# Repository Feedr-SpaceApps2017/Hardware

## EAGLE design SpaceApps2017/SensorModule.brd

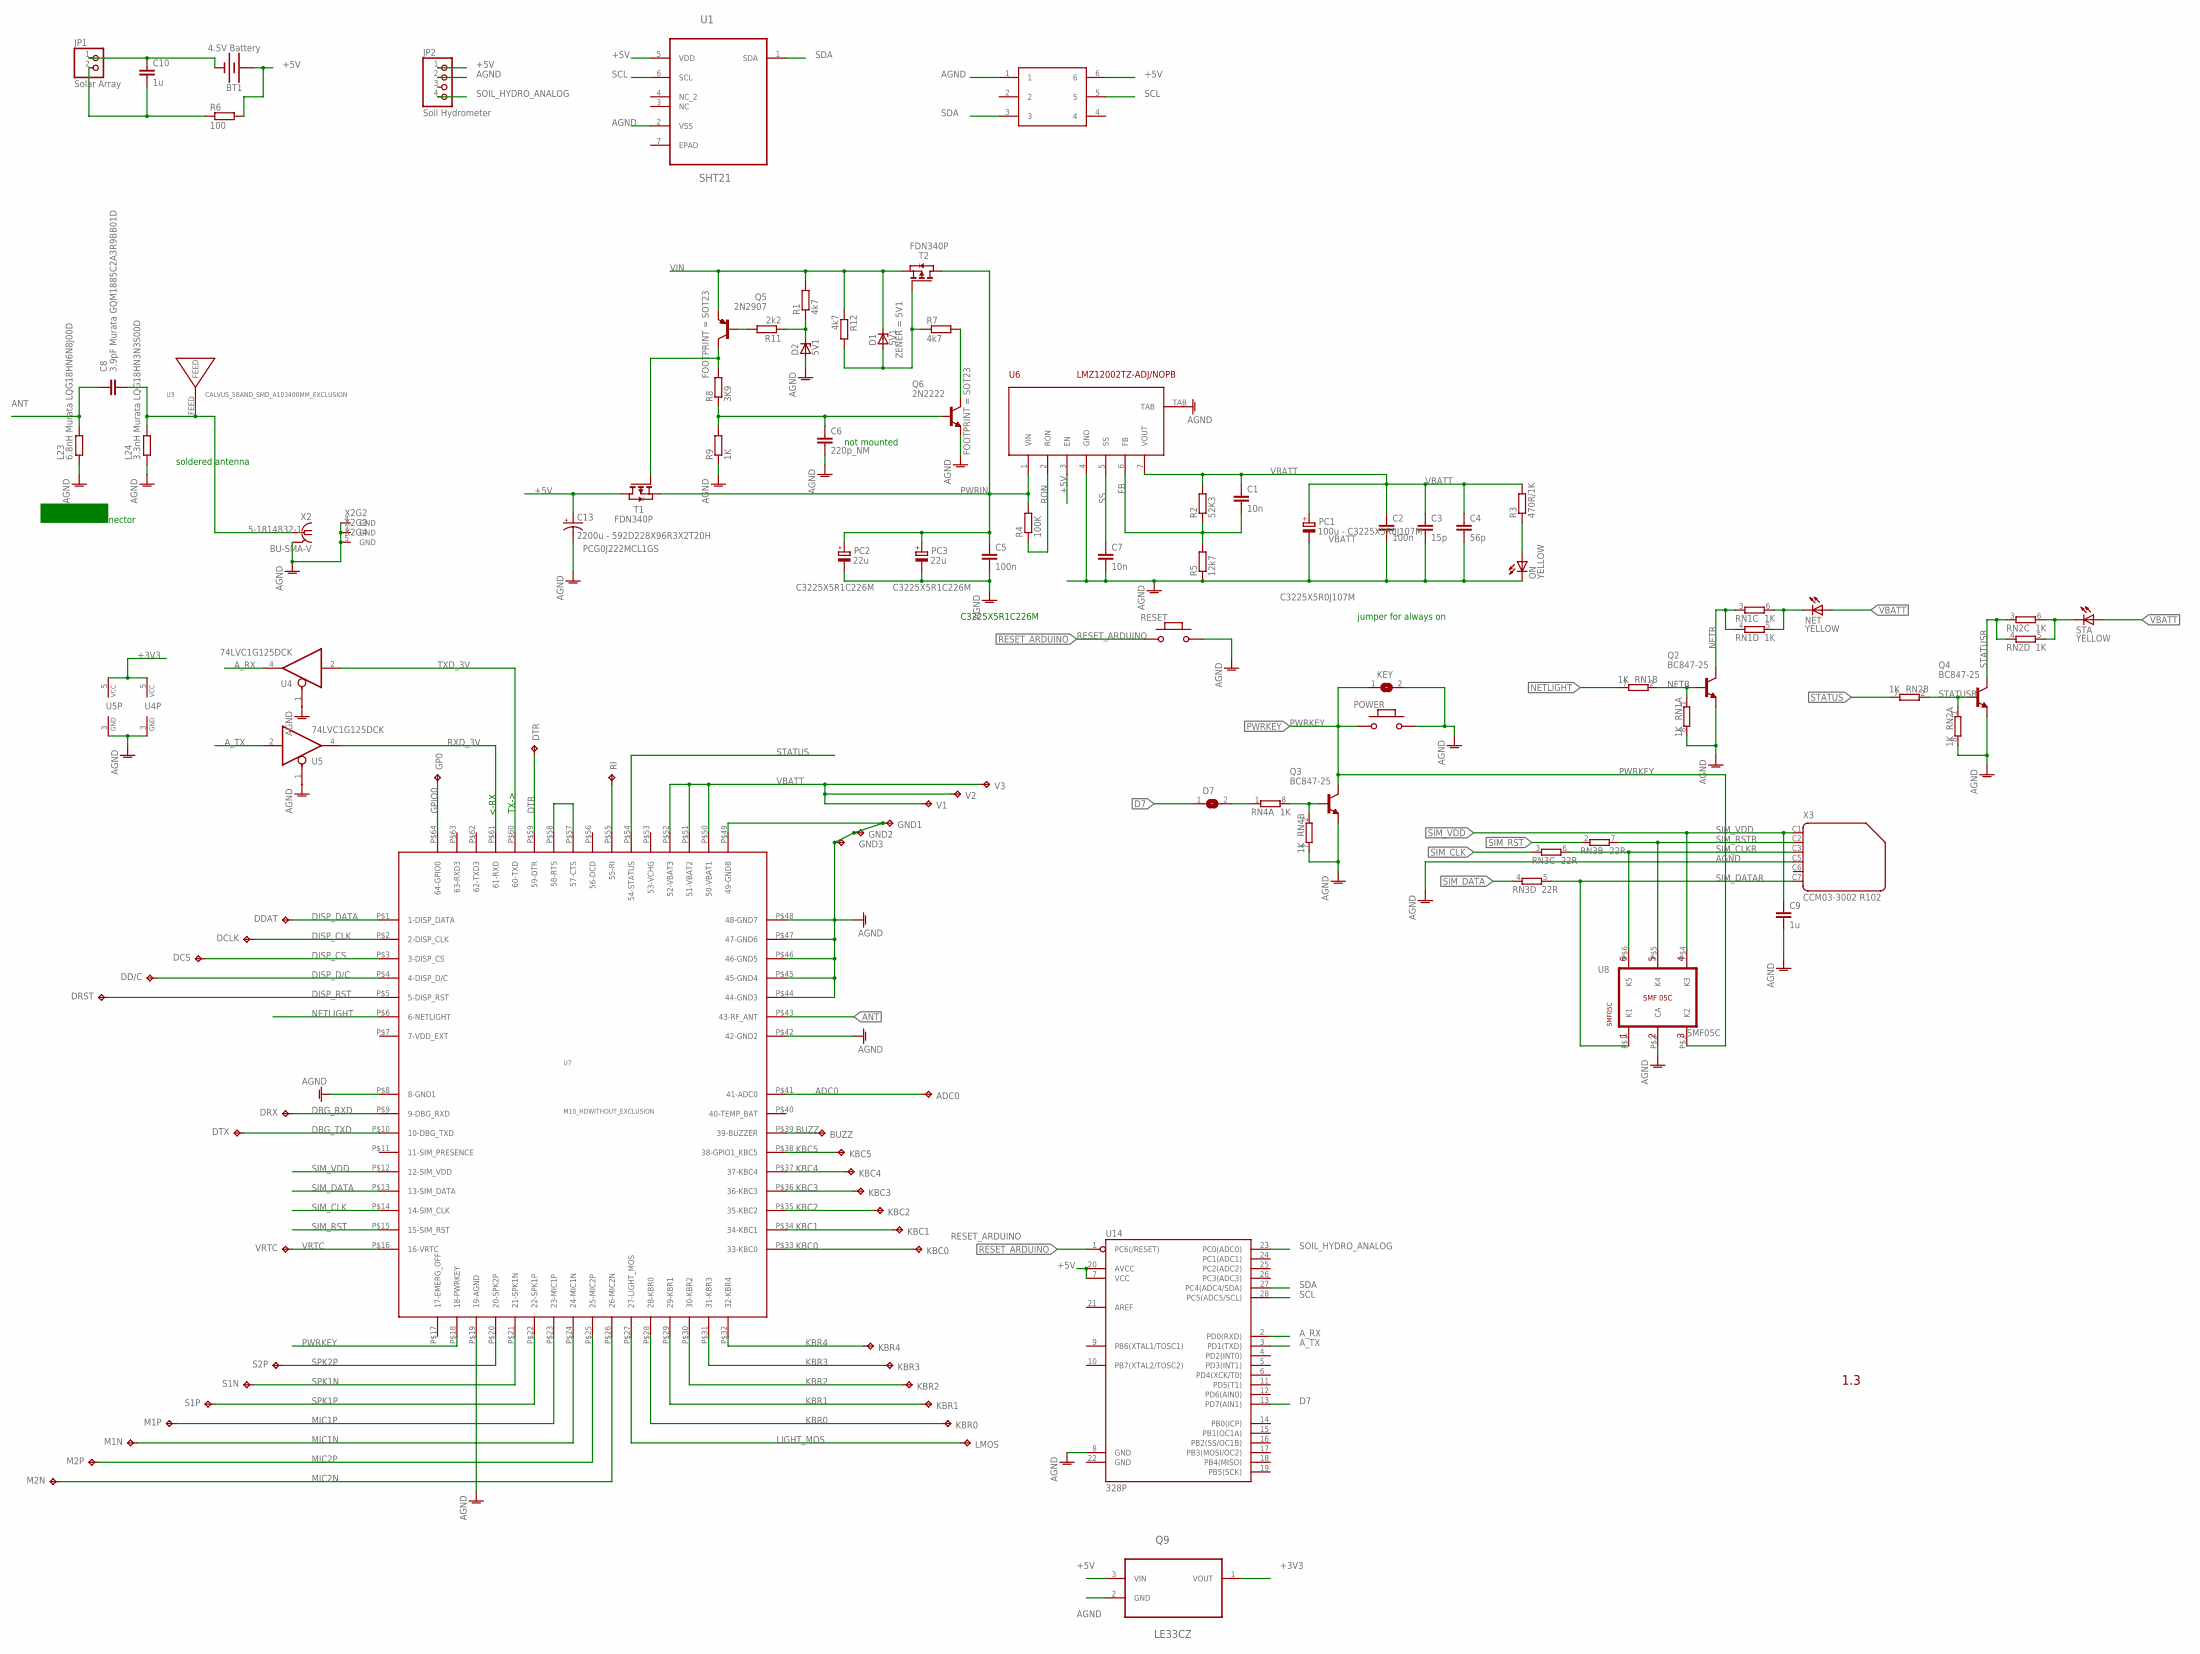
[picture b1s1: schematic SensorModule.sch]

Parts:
ADC0: TPPAD1-09; P1-09
BT1: 4.5V Battery; BATTERY-AA
BUZZ: TPPAD1-09; P1-09
C1, C7: 10n; C0603-ROUND
C2, C5: 100n; C0603-ROUND
C3: 15p; C0603-ROUND
C4: 56p; C0603-ROUND
C6: 220p_NM; C0603-ROUND
C8: 3.9pF Murata GQM1885C2A3R9BB01D; C0603-ROUND
C9: 1u; C0603-ROUND
C10: 1u; C0201
C13: 2200u - 592D228X96R3X2T20H; 085CS_1AW
D1, D2: 5V1; SMB
D7: SJ
DCLK: TPPAD1-09; P1-09
DCS: TPPAD1-09; P1-09
DD/C: TPPAD1-09; P1-09
DDAT: TPPAD1-09; P1-09
DRST: TPPAD1-09; P1-09
DRX: TPPAD1-09; P1-09
DTR: TPPAD1-09; P1-09
DTX: TPPAD1-09; P1-09
GND1, GND2, GND3: TPPAD1-09; P1-09
GP0: TPPAD1-09; P1-09
JP1: Solar Array; 1X02
JP2: Soil Hydrometer; 1X04
KBC0, KBC1, KBC2, KBC3, KBC4, KBC5: TPPAD1-09; P1-09
KBR0, KBR1, KBR2, KBR3, KBR4: TPPAD1-09; P1-09
KEY: SJ
L23: 6.8nH Murata LQG18HN6N8J00D; R0603-ROUND
L24: 3.3nH Murata LQG18HN3N3S00D; R0603-ROUND
LMOS: TPPAD1-09; P1-09
M1N, M1P, M2N, M2P: TPPAD1-09; P1-09
NET: YELLOW; CHIP-LED0805
ON: YELLOW; CHIP-LED0805
PC1: 100u - C3225X5R0J107M; SMC_B
PC2, PC3: 22u; SMC_B
POWER: MYSMD_PB157; SMD_157SW
Q2, Q3, Q4: BC847-25; SOT23-BEC
Q5: 2N2907; SOT23-BEC
Q6: 2N2222; SOT23-BEC
Q9: LE33CZ; TO127P254X749-3
R1, R7, R12: 4k7; R0603-ROUND
R2: 52K3; R0603-ROUND
R3: 470R/1K; R0603-ROUND
R4: 100K; R0603-ROUND
R5: 12k7; R0603-ROUND
R6: 100; R0201
R8: 3K9; R0603-ROUND
R9: 1K; R0603-ROUND
R11: 2k2; R0603-ROUND
RESET: MYSMD_PB157; SMD_157SW
RI: TPPAD1-09; P1-09
RN1, RN2, RN4: 1K; CAY16
RN3: 22R; CAY16
S1N, S1P, S2P: TPPAD1-09; P1-09
STA: YELLOW; CHIP-LED0805
T1, T2: FDN340P; SOT-23
U1: SHT21; DFN300X300X110-7N
U3: CALVUS_5BAND_SMD_A103400MM_EXCLUSION; CALVUS_5BAND_SMD_A10340_0MM_EXCLUSION
U4, U5: 74LVC1G125DCK; SC70-5
U6: LMZ12002TZ-ADJ/NOPB; TZA-7
U7: M10_HDWITHOUT_EXCLUSION; M10_HD_WITHOUT_EXCLUSION
U8: SMF05C; SC70_6L
U14: 328P; DIP28
U$1: VISHAY_VEML6070; SOT-23-6
V1, V2, V3: TPPAD1-09; P1-09
VRTC: TPPAD1-09; P1-09
X2: BU-SMA-V
X3: CCM03-3002 R102; CON-AMPHENOL_C707_10M006_512_2

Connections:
+3V3: Q9.1 (VOUT), U4.5 (VCC), U5.5 (VCC)
+5V: BT1.PWR@1 (+), C13.+, JP2.1, Q9.3 (VIN), R6.2, T1.1 (D), U1.5 (VDD), U6.3 (EN), U14.7 (VCC), U14.20 (AVCC), U$1.6
ADC0: ADC0.TP, U7.P$41 (41-ADC0)
AGND: BT1.GND@1 (-), C2.2, C3.2, C4.2, C5.2, C6.2, C7.2, C9.2, C10.1, C13.-, D2.A, GND1.TP, GND2.TP, GND3.TP, JP1.1, JP2.2, KEY.2, L23.1, L24.1, ON.C, PC1.-, PC2.-, PC3.-, POWER.2, Q2.E, Q3.E, Q4.E, Q6.E, Q9.2 (GND), R5.1, R9.1, RESET.2, RN1.8 (2), RN2.8 (2), RN4.7 (2), U1.2 (VSS), U4.1 (OE), U4.3 (GND), U5.1 (OE), U5.3 (GND), U6.4 (GND), U6.TAB, U7.P$8 (8-GND1), U7.P$19 (19-AGND), U7.P$42 (42-GND2), U7.P$44 (44-GND3), U7.P$45 (45-GND4), U7.P$46 (46-GND5), U7.P$47 (47-GND6), U7.P$48 (48-GND7), U7.P$49 (49-GND8), U8.P$2 (CA), U14.8 (GND), U$1.1, X2.2 (GND), X2.3 (GND), X2.4 (GND), X2.5 (GND), X3.C5 (4)
ANT: C8.1, L23.2, U7.P$43 (43-RF_ANT)
ANTENA: C8.2, L24.2, U3.FEED, X2.1
A_RX: U4.4 (O), U14.2 (PD0(RXD))
A_TX: U5.2 (I), U14.3 (PD1(TXD))
BUZZ: BUZZ.TP, U7.P$39 (39-BUZZER)
D7: D7.1, U14.13 (PD7(AIN1))
DBG_RXD: DRX.TP, U7.P$9 (9-DBG_RXD)
DBG_TXD: DTX.TP, U7.P$10 (10-DBG_TXD)
DISP_CLK: DCLK.TP, U7.P$2 (2-DISP_CLK)
DISP_CS: DCS.TP, U7.P$3 (3-DISP_CS)
DISP_D/C: DD/C.TP, U7.P$4 (4-DISP_D/C)
DISP_DATA: DDAT.TP, U7.P$1 (1-DISP_DATA)
DISP_RST: DRST.TP, U7.P$5 (5-DISP_RST)
DTR: DTR.TP, U7.P$59 (59-DTR)
FB: C1.2, R2.1, R5.2, U6.6 (FB)
GPIO0: GP0.TP, U7.P$64 (64-GPIO0)
KBC0: KBC0.TP, U7.P$33 (33-KBC0)
KBC1: KBC1.TP, U7.P$34 (34-KBC1)
KBC2: KBC2.TP, U7.P$35 (35-KBC2)
KBC3: KBC3.TP, U7.P$36 (36-KBC3)
KBC4: KBC4.TP, U7.P$37 (37-KBC4)
KBC5: KBC5.TP, U7.P$38 (38-GPIO1_KBC5)
KBR0: KBR0.TP, U7.P$28 (28-KBR0)
KBR1: KBR1.TP, U7.P$29 (29-KBR1)
KBR2: KBR2.TP, U7.P$30 (30-KBR2)
KBR3: KBR3.TP, U7.P$31 (31-KBR3)
KBR4: KBR4.TP, U7.P$32 (32-KBR4)
LIGHT_MOS: LMOS.TP, U7.P$27 (27-LIGHT_MOS)
MIC1N: M1N.TP, U7.P$24 (24-MIC1N)
MIC1P: M1P.TP, U7.P$23 (23-MIC1P)
MIC2N: M2N.TP, U7.P$26 (26-MIC2N)
MIC2P: M2P.TP, U7.P$25 (25-MIC2P)
unnamed: C10.2, JP1.2, R6.1
unnamed: ON.A, R3.1
unnamed: Q3.B, RN4.2 (1), RN4.8 (2)
unnamed: U7.P$57 (57-CTS), U7.P$58 (58-RTS)
unnamed: D7.2, RN4.1
unnamed: RI.TP, U7.P$55 (55-RI)
unnamed: Q5.C, R8.2, T1.3 (G)
unnamed: Q6.C, R7.2
unnamed: C6.1, Q6.B, R8.1, R9.2
unnamed: Q5.B, R11.2
unnamed: D1.A, R7.1, R12.2, T2.3 (G)
unnamed: D2.C, R1.1, R11.1
NETB: Q2.B, RN1.1, RN1.2 (1)
NETL: NET.C, RN1.5 (2), RN1.6 (2)
NETLIGHT: RN1.7 (2), U7.P$6 (6-NETLIGHT)
NETR: Q2.C, RN1.3 (1), RN1.4 (1)
PWRIN: C5.1, PC2.+, PC3.+, R4.2, T1.2 (S), T2.1 (D), U6.1 (VIN)
PWRKEY: KEY.1, POWER.1, Q3.C, U7.P$18 (18-PWRKEY), U8.P$3 (K2)
RESET_ARDUINO: RESET.1, U14.1 (PC6(/RESET))
RON: R4.1, U6.2 (RON)
RXD_3V: U5.4 (O), U7.P$61 (61-RXD)
SCL: U1.6 (SCL), U14.28 (PC5(ADC5/SCL)), U$1.5
SDA: U1.1 (SDA), U14.27 (PC4(ADC4/SDA)), U$1.3
SIM_CLK: RN3.3 (1), U7.P$14 (14-SIM_CLK)
SIM_CLKR: RN3.6 (2), U8.P$6 (K5), X3.C3 (3)
SIM_DATA: RN3.4 (1), U7.P$13 (13-SIM_DATA)
SIM_DATAR: RN3.5 (2), U8.P$1 (K1), X3.C7 (6)
SIM_RST: RN3.2 (1), U7.P$15 (15-SIM_RST)
SIM_RSTR: RN3.7 (2), U8.P$5 (K4), X3.C2 (2)
SIM_VDD: C9.1, U7.P$12 (12-SIM_VDD), U8.P$4 (K3), X3.C1 (1)
SOIL_HYDRO_ANALOG: JP2.4, U14.23 (PC0(ADC0))
SPK1N: S1N.TP, U7.P$21 (21-SPK1N)
SPK1P: S1P.TP, U7.P$22 (22-SPK1P)
SPK2P: S2P.TP, U7.P$20 (20-SPK2P)
SS: C7.1, U6.5 (SS)
STATUS: RN2.7 (2), U7.P$54 (54-STATUS)
STATUSB: Q4.B, RN2.1, RN2.2 (1)
STATUSL: RN2.5 (2), RN2.6 (2), STA.C
STATUSR: Q4.C, RN2.3 (1), RN2.4 (1)
TXD_3V: U4.2 (I), U7.P$60 (60-TXD)
VBATT: C1.1, C2.1, C3.1, C4.1, NET.A, PC1.+, R2.2, R3.2, STA.A, U6.7 (VOUT), U7.P$50 (50-VBAT1), U7.P$51 (51-VBAT2), U7.P$52 (52-VBAT3), V1.TP, V2.TP, V3.TP
VIN: D1.C, Q5.E, R1.2, R12.1, T2.2 (S)
VRTC: U7.P$16 (16-VRTC), VRTC.TP

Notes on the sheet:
soldered antenna
SMA or U.FL connector
jumper for always on
SMF05C
TX->
<-RX
C3225X5R1C226M
PCG0J222MCL1GS
not mounted
1.3

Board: 4 copper layers, 100 parts (0 on the bottom side), 79 nets, no tracks yet.

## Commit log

2017-04-30 Done circuit, PCB, 3D model of PCB
2017-04-30 Added PNG of circuit
2017-04-30 added lower res circuit schematic

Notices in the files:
parts and their libraries:
SparkFun-Batteries: Licensing: Creative Commons ShareAlike 4.0 International - https://creativecommons.org/licenses/by-sa/4.0
